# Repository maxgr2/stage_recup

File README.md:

# Projet de Surveillance de Batteries

## Introduction 

Ce repo a été réalisé dans le cadre d'un stage de 4ème année d'école d'ingénieurs à l'**École de Technologie Supérieure (ÉTS) de Montréal**, au sein du laboratoire **LACIME**, par un étudiant de **Polytech Grenoble**.
Si vous souhaitez avoir plus de détails sur le contenu de chaque projet merci de suivre les dossier projet_batterie et projet_salle_blanche.
Le dossier contient aussi tous les fichiers Kicad, Le dossier Kicad contient les évolutions des différentes cartes produites et la dernière version est celle à jour pour le projet batterie.
Le dossier Kicad esp maitre est le dossier principale pour le projet salle blanche.

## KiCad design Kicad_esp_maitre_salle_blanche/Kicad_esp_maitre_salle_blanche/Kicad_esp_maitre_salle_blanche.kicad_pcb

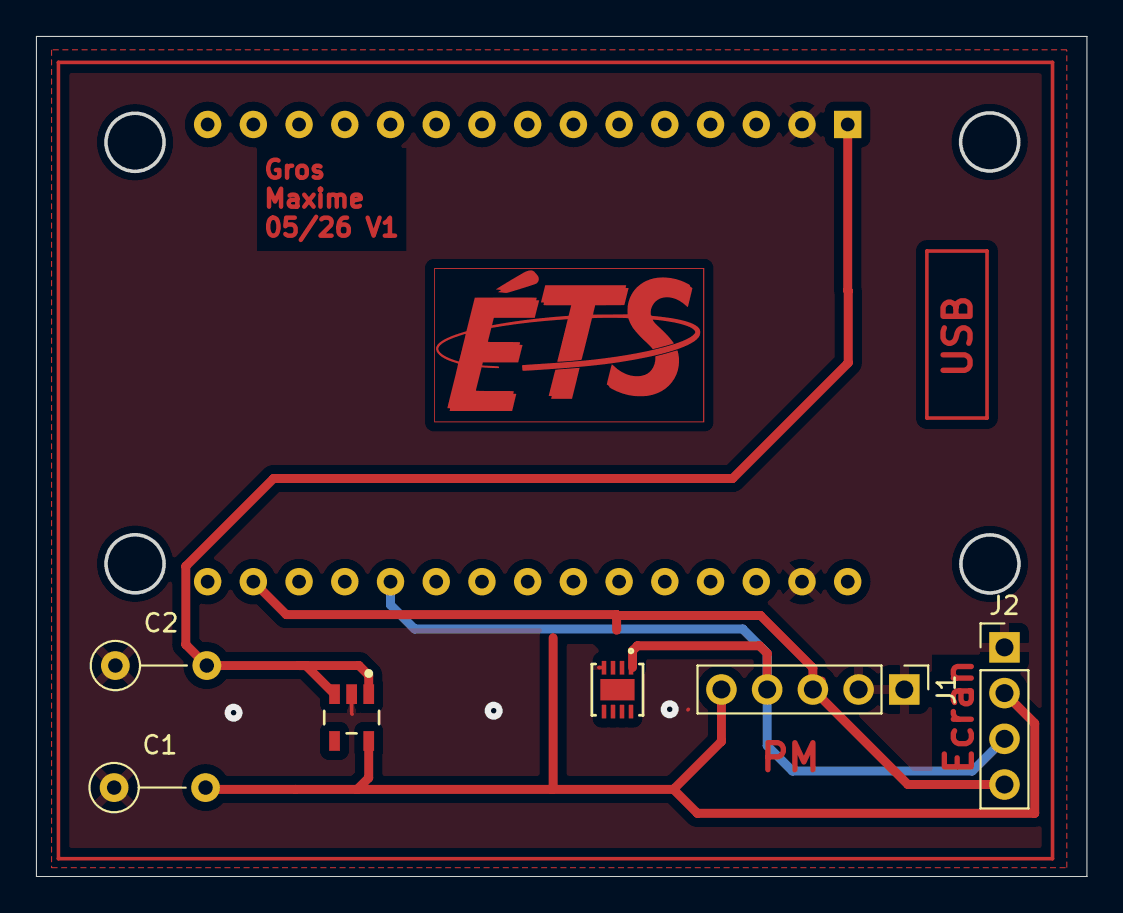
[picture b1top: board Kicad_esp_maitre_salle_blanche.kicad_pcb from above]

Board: 2 copper layers, 58.4 x 46.7 mm, 7 parts (1 on the bottom side), 5 nets.

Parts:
C1, C2: C; R_Axial_DIN0207_L6.3mm_D2.5mm_P5.08mm_Vertical
J1: Conn_01x05_Pin; PinHeader_1x05_P2.54mm_Vertical
J2: Conn_01x04_Pin; PinHeader_1x04_P2.54mm_Vertical
U1: esp32_devkit_v1_doit
U2: TLV75533PDYDR; DBV0005A-MFG
U3: SHT40-CD1B-R3; U_SHT3_SEN

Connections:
5V: C2.2, U1.1 (VIN), U2.1 (IN), U2.3 (EN)
5V_LDO: C1.2, J1.5, J2.2, U2.5 (OUT), U3.3 (VDD)
GND: C1.1, C2.1, J1.1, J1.2, J2.1, U1.2 (GND), U1.17 (GND), U2.2 (GND), U3.4 (VSS)
SCL: J1.3, J2.4, U1.29 (GPIO22), U3.2 (SCL)
SDA: J1.4, J2.3, U1.26 (GPIO21), U3.1 (SDA)

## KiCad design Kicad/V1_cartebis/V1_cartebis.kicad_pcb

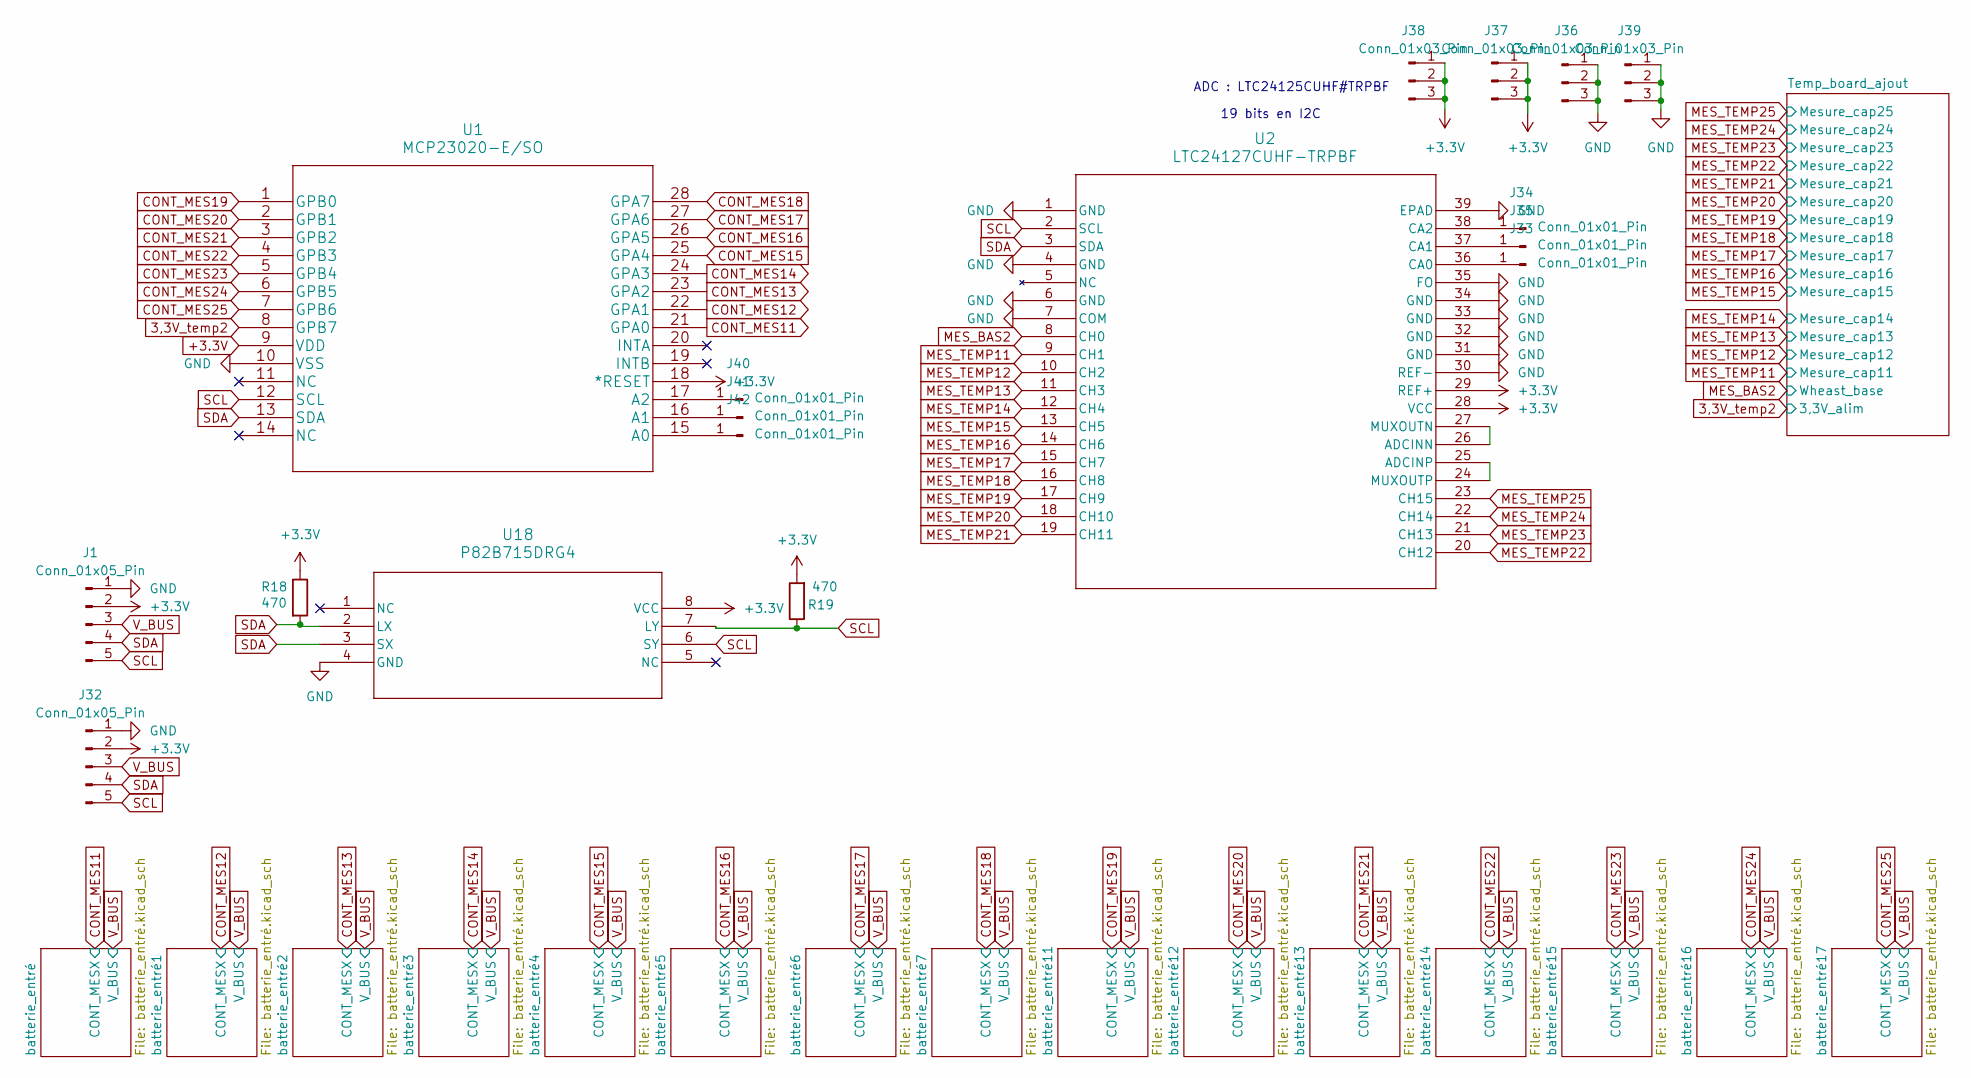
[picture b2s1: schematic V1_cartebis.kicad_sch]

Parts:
J1, J32: Conn_01x05_Pin; PinHeader_1x05_P2.54mm_Vertical
J33, J34, J35, J40, J41, J42: Conn_01x01_Pin; PinHeader_1x01_P1.00mm_Vertical
J36, J37, J38, J39: Conn_01x03_Pin; PinHeader_1x03_P1.00mm_Vertical
R18, R19: 470; R_Axial_DIN0207_L6.3mm_D2.5mm_P10.16mm_Horizontal
U1: MCP23020-E/SO; MCP23017T-E&slash_SO
U2: LTC24127CUHF-TRPBF; QFN-38_UHF_LIT
U18: P82B715DRG4

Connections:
3,3V_temp2: U1.8 (GPB7); also elsewhere on the board
+3.3V: J1.2, J32.2, J37.1, J37.2, J37.3, J38.1, J38.2, J38.3, R18.1, R19.2, U1.9 (VDD), U1.18 (*RESET), U2.28 (VCC), U2.29 (REF+), U18.8 (VCC)
CONT_MES11: U1.21 (GPA0); also elsewhere on the board
CONT_MES12: U1.22 (GPA1); also elsewhere on the board
CONT_MES13: U1.23 (GPA2); also elsewhere on the board
CONT_MES14: U1.24 (GPA3); also elsewhere on the board
CONT_MES15: U1.25 (GPA4); also elsewhere on the board
CONT_MES16: U1.26 (GPA5); also elsewhere on the board
CONT_MES17: U1.27 (GPA6); also elsewhere on the board
CONT_MES18: U1.28 (GPA7); also elsewhere on the board
CONT_MES19: U1.1 (GPB0); also elsewhere on the board
CONT_MES20: U1.2 (GPB1); also elsewhere on the board
CONT_MES21: U1.3 (GPB2); also elsewhere on the board
CONT_MES22: U1.4 (GPB3); also elsewhere on the board
CONT_MES23: U1.5 (GPB4); also elsewhere on the board
CONT_MES24: U1.6 (GPB5); also elsewhere on the board
CONT_MES25: U1.7 (GPB6); also elsewhere on the board
GND: J1.1, J32.1, J36.1, J36.2, J36.3, J39.1, J39.2, J39.3, U1.10 (VSS), U2.1 (GND), U2.4 (GND), U2.6 (GND), U2.7 (COM), U2.30 (REF-), U2.31 (GND), U2.32 (GND), U2.33 (GND), U2.34 (GND), U2.35 (FO), U2.39 (EPAD), U18.4 (GND); also elsewhere on the board
MES_BAS2: U2.8 (CH0); also elsewhere on the board
MES_TEMP11: U2.9 (CH1); also elsewhere on the board
MES_TEMP12: U2.10 (CH2); also elsewhere on the board
MES_TEMP13: U2.11 (CH3); also elsewhere on the board
MES_TEMP14: U2.12 (CH4); also elsewhere on the board
MES_TEMP15: U2.13 (CH5); also elsewhere on the board
MES_TEMP16: U2.14 (CH6); also elsewhere on the board
MES_TEMP17: U2.15 (CH7); also elsewhere on the board
MES_TEMP18: U2.16 (CH8); also elsewhere on the board
MES_TEMP19: U2.17 (CH9); also elsewhere on the board
MES_TEMP20: U2.18 (CH10); also elsewhere on the board
MES_TEMP21: U2.19 (CH11); also elsewhere on the board
MES_TEMP22: U2.20 (CH12); also elsewhere on the board
MES_TEMP23: U2.21 (CH13); also elsewhere on the board
MES_TEMP24: U2.22 (CH14); also elsewhere on the board
MES_TEMP25: U2.23 (CH15); also elsewhere on the board
unnamed: J33.1, U2.36 (CA0)
unnamed: J34.1, U2.38 (CA2)
unnamed: J35.1, U2.37 (CA1)
unnamed: J40.1, U1.17 (A2)
unnamed: J41.1, U1.16 (A1)
unnamed: J42.1, U1.15 (A0)
unnamed: U2.26 (ADCINN), U2.27 (MUXOUTN)
unnamed: U2.24 (MUXOUTP), U2.25 (ADCINP)
SCL: J1.5, J32.5, R19.1, U1.12 (SCL), U2.2 (SCL), U18.6 (SY), U18.7 (LY)
SDA: J1.4, J32.4, R18.2, U1.13 (SDA), U2.3 (SDA), U18.2 (LX), U18.3 (SX)
V_BUS: J1.3, J32.3; also elsewhere on the board

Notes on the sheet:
19 bits en I2C
ADC : LTC24125CUHF#TRPBF

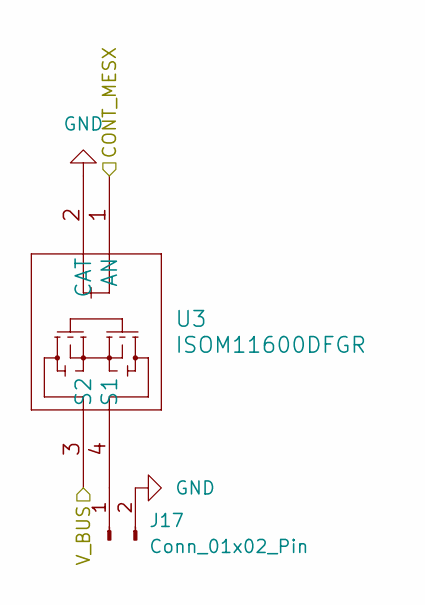
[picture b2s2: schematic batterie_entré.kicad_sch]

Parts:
J17: Conn_01x02_Pin; PinHeader_1x02_P2.54mm_Vertical
U3: ISOM11600DFGR; ISOM8600DFGR

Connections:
CONT_MES19: U3.1 (AN); also elsewhere on the board
GND: J17.2, U3.2 (CAT); also elsewhere on the board
unnamed: J17.1, U3.4 (S1)
V_BUS: U3.3 (S2); also elsewhere on the board

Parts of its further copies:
J18, J19, J20, J21, J22, J23, J24, J25, J26, J27, J28, J29, J30, J31: Conn_01x02_Pin; PinHeader_1x02_P2.54mm_Vertical
U4, U5, U6, U7, U8, U9, U10, U11, U12, U13, U14, U15, U16, U17: ISOM11600DFGR; ISOM8600DFGR

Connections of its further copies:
CONT_MES11: U14.1 (AN); also elsewhere on the board
CONT_MES12: U15.1 (AN); also elsewhere on the board
CONT_MES13: U16.1 (AN); also elsewhere on the board
CONT_MES14: U17.1 (AN); also elsewhere on the board
CONT_MES15: U11.1 (AN); also elsewhere on the board
CONT_MES16: U10.1 (AN); also elsewhere on the board
CONT_MES17: U13.1 (AN); also elsewhere on the board
CONT_MES18: U12.1 (AN); also elsewhere on the board
CONT_MES20: U4.1 (AN); also elsewhere on the board
CONT_MES21: U9.1 (AN); also elsewhere on the board
CONT_MES22: U8.1 (AN); also elsewhere on the board
CONT_MES23: U6.1 (AN); also elsewhere on the board
CONT_MES24: U5.1 (AN); also elsewhere on the board
CONT_MES25: U7.1 (AN); also elsewhere on the board
GND: J18.2, J19.2, J20.2, J21.2, J22.2, J23.2, J24.2, J25.2, J26.2, J27.2, J28.2, J29.2, J30.2, J31.2, U4.2 (CAT), U5.2 (CAT), U6.2 (CAT), U7.2 (CAT), U8.2 (CAT), U9.2 (CAT), U10.2 (CAT), U11.2 (CAT), U12.2 (CAT), U13.2 (CAT), U14.2 (CAT), U15.2 (CAT), U16.2 (CAT), U17.2 (CAT); also elsewhere on the board
unnamed: J18.1, U4.4 (S1)
unnamed: J19.1, U5.4 (S1)
unnamed: J20.1, U6.4 (S1)
unnamed: J21.1, U7.4 (S1)
unnamed: J22.1, U8.4 (S1)
unnamed: J23.1, U9.4 (S1)
unnamed: J24.1, U10.4 (S1)
unnamed: J25.1, U11.4 (S1)
unnamed: J26.1, U12.4 (S1)
unnamed: J27.1, U13.4 (S1)
unnamed: J28.1, U14.4 (S1)
unnamed: J29.1, U15.4 (S1)
unnamed: J30.1, U16.4 (S1)
unnamed: J31.1, U17.4 (S1)
V_BUS: U4.3 (S2), U5.3 (S2), U6.3 (S2), U7.3 (S2), U8.3 (S2), U9.3 (S2), U10.3 (S2), U11.3 (S2), U12.3 (S2), U13.3 (S2), U14.3 (S2), U15.3 (S2), U16.3 (S2), U17.3 (S2); also elsewhere on the board

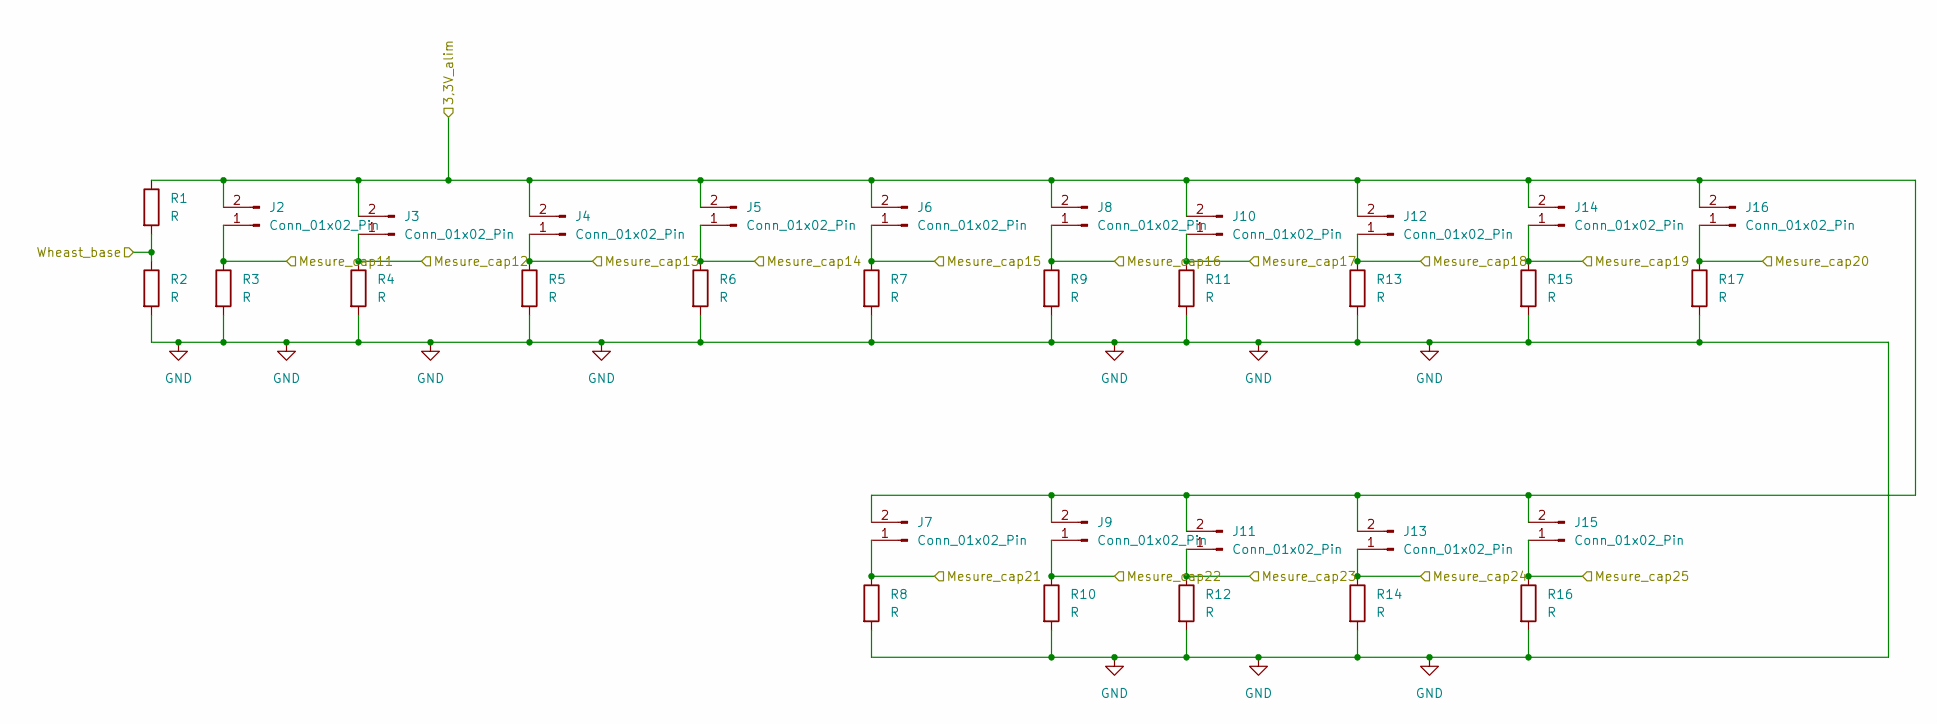
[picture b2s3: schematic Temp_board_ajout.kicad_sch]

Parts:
J2, J3, J4, J5, J6, J7, J8, J9, J10, J11, J12, J13, J14, J15, J16: Conn_01x02_Pin; PinHeader_1x02_P2.54mm_Vertical
R1, R2, R3, R4, R5, R6, R7, R8, R9, R10, R11, R12, R13, R14, R15, R16, R17: R; R_Axial_DIN0207_L6.3mm_D2.5mm_P10.16mm_Horizontal

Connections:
3,3V_temp2: J2.2, J3.2, J4.2, J5.2, J6.2, J7.2, J8.2, J9.2, J10.2, J11.2, J12.2, J13.2, J14.2, J15.2, J16.2, R1.1; also elsewhere on the board
GND: R2.2, R3.2, R4.2, R5.2, R6.2, R7.2, R8.2, R9.2, R10.2, R11.2, R12.2, R13.2, R14.2, R15.2, R16.2, R17.2; also elsewhere on the board
MES_BAS2: R1.2, R2.1; also elsewhere on the board
MES_TEMP11: J2.1, R3.1; also elsewhere on the board
MES_TEMP12: J3.1, R4.1; also elsewhere on the board
MES_TEMP13: J4.1, R5.1; also elsewhere on the board
MES_TEMP14: J5.1, R6.1; also elsewhere on the board
MES_TEMP15: J6.1, R7.1; also elsewhere on the board
MES_TEMP16: J8.1, R9.1; also elsewhere on the board
MES_TEMP17: J10.1, R11.1; also elsewhere on the board
MES_TEMP18: J12.1, R13.1; also elsewhere on the board
MES_TEMP19: J14.1, R15.1; also elsewhere on the board
MES_TEMP20: J16.1, R17.1; also elsewhere on the board
MES_TEMP21: J7.1, R8.1; also elsewhere on the board
MES_TEMP22: J9.1, R10.1; also elsewhere on the board
MES_TEMP23: J11.1, R12.1; also elsewhere on the board
MES_TEMP24: J13.1, R14.1; also elsewhere on the board
MES_TEMP25: J15.1, R16.1; also elsewhere on the board

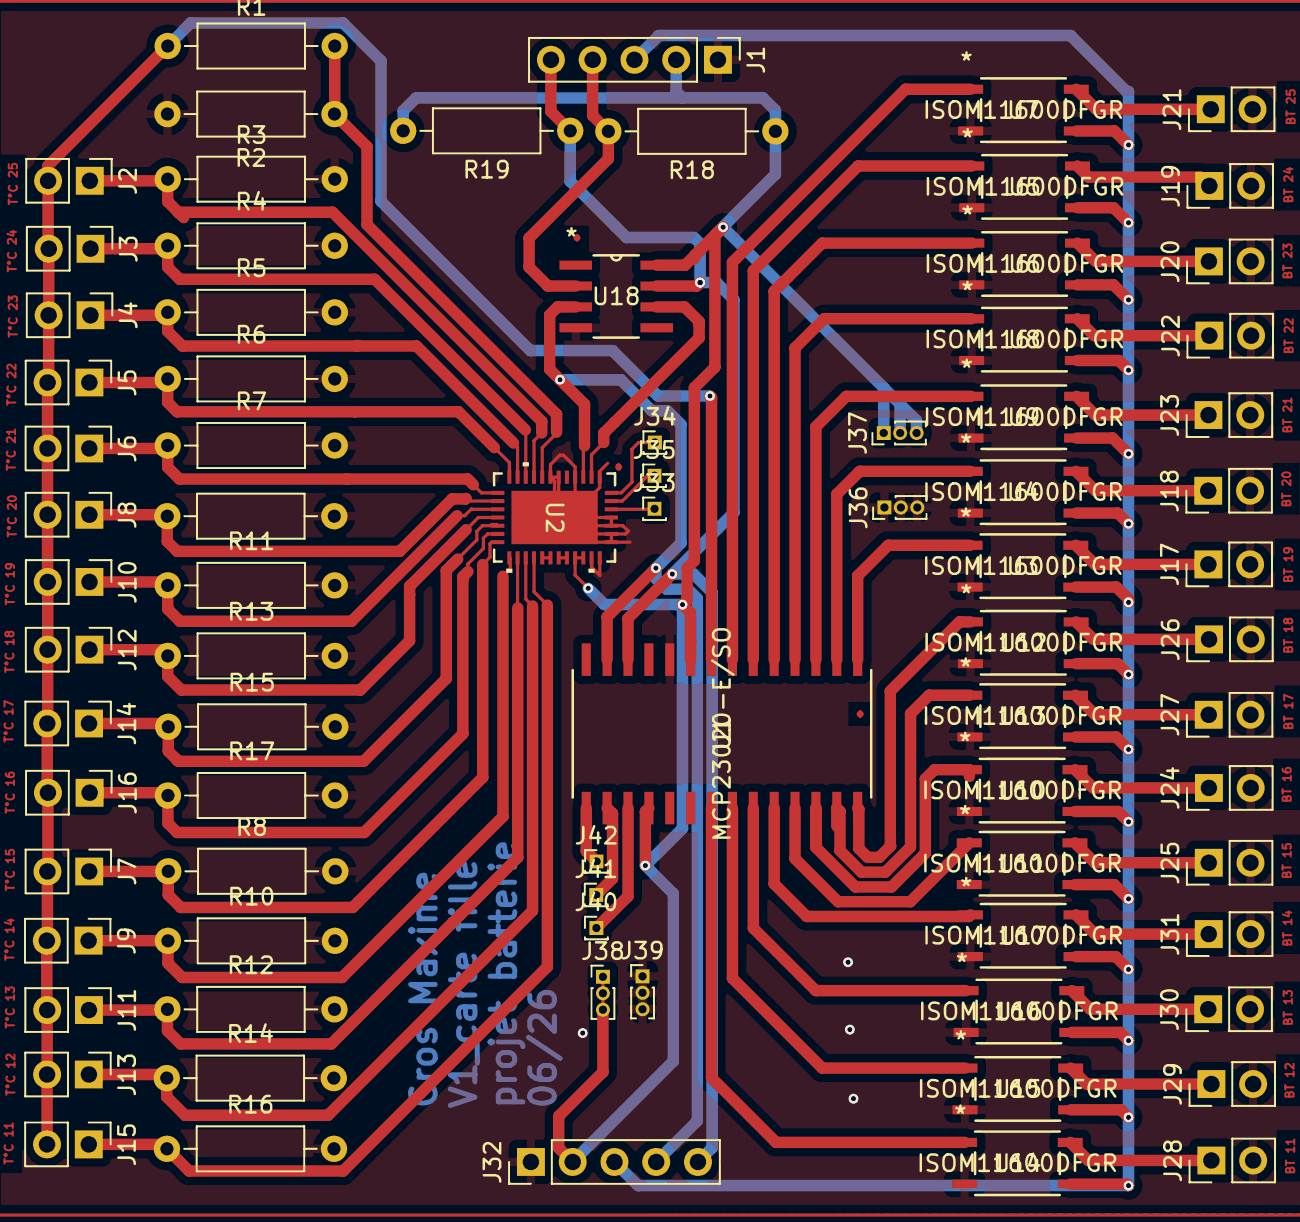
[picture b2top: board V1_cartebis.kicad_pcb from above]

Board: 2 copper layers, 79 parts (0 on the bottom side), 60 nets.

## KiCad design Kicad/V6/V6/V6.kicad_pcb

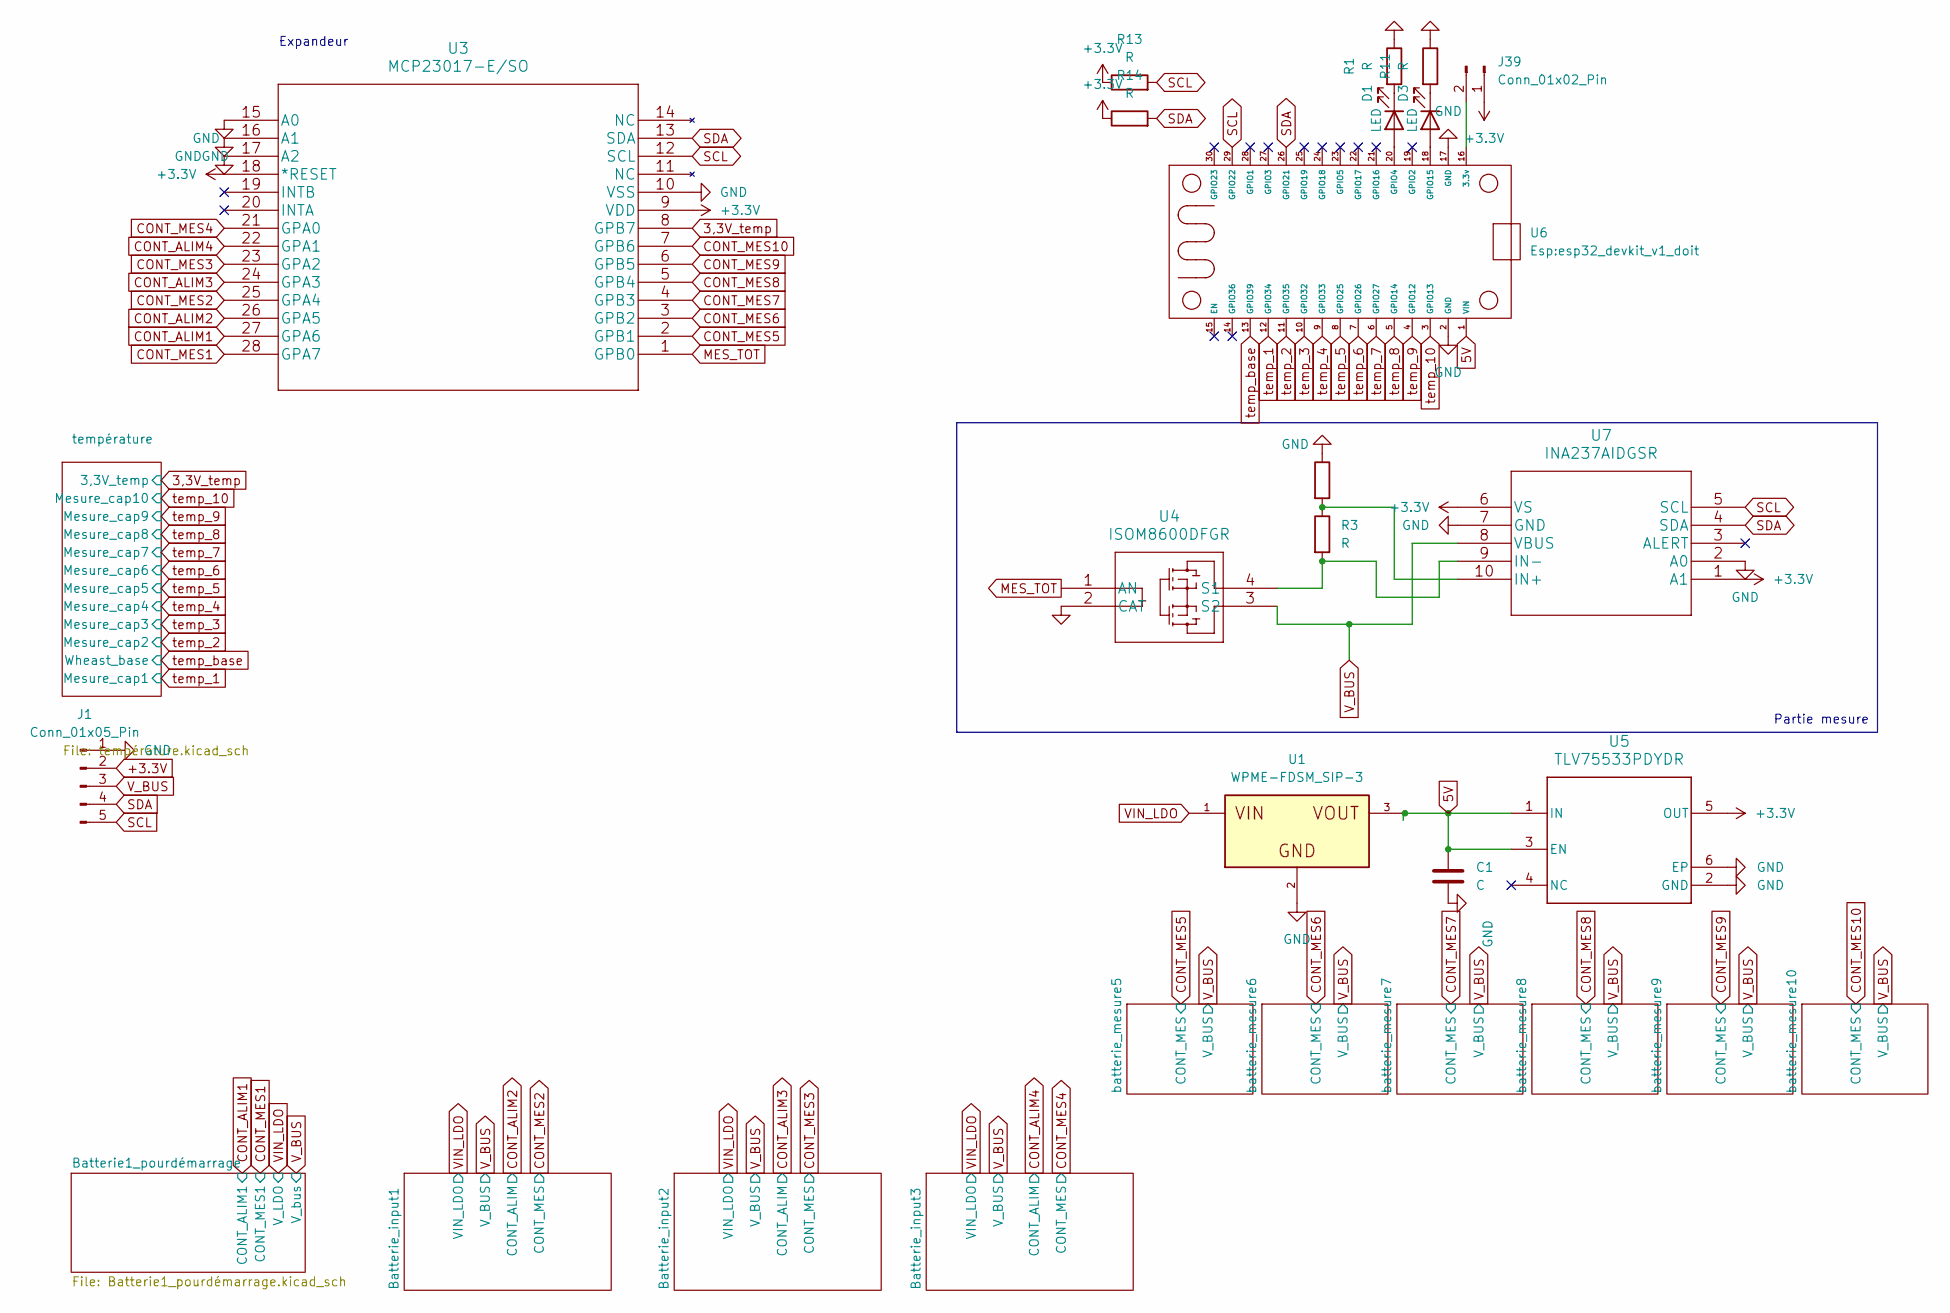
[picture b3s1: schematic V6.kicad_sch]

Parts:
C1: C; R_Axial_DIN0207_L6.3mm_D2.5mm_P5.08mm_Vertical
D1, D3: LED; PinHeader_1x02_P2.54mm_Vertical
J1: Conn_01x05_Pin; PinHeader_1x05_P2.54mm_Vertical
J39: Conn_01x02_Pin; PinHeader_1x02_P2.54mm_Vertical
R1, R11, R13, R14: R; R_Axial_DIN0207_L6.3mm_D2.5mm_P10.16mm_Horizontal
R2: 2,2Kohms; R_Axial_DIN0309_L9.0mm_D3.2mm_P20.32mm_Horizontal
R3: R; R_Axial_DIN0411_L9.9mm_D3.6mm_P20.32mm_Horizontal
U1: WPME-FDSM_SIP-3; WPME-FDSM_173950575
U3: MCP23017-E/SO; MCP23017T-E&slash_SO
U4: ISOM8600DFGR
U5: TLV75533PDYDR
U6: esp32_devkit_v1_doit
U7: INA237AIDGSR

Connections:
3,3V_temp: U3.8 (GPB7); also elsewhere on the board
5V: C1.2, U1.3, U5.1 (IN), U5.3 (EN), U6.1 (VIN)
+3.3V: J1.2, J39.1, R13.1, R14.1, U3.9 (VDD), U3.18 (*RESET), U5.5 (OUT), U7.1 (A1), U7.6 (VS)
CONT_ALIM1: U3.27 (GPA6); also elsewhere on the board
CONT_ALIM2: U3.26 (GPA5); also elsewhere on the board
CONT_ALIM3: U3.24 (GPA3); also elsewhere on the board
CONT_ALIM4: U3.22 (GPA1); also elsewhere on the board
CONT_MES1: U3.28 (GPA7); also elsewhere on the board
CONT_MES2: U3.25 (GPA4); also elsewhere on the board
CONT_MES3: U3.23 (GPA2); also elsewhere on the board
CONT_MES4: U3.21 (GPA0); also elsewhere on the board
CONT_MES5: U3.2 (GPB1); also elsewhere on the board
CONT_MES6: U3.3 (GPB2); also elsewhere on the board
CONT_MES7: U3.4 (GPB3); also elsewhere on the board
CONT_MES8: U3.5 (GPB4); also elsewhere on the board
CONT_MES9: U3.6 (GPB5); also elsewhere on the board
CONT_MES10: U3.7 (GPB6); also elsewhere on the board
GND: C1.1, J1.1, R1.1, R2.1, R11.1, U1.2, U3.10 (VSS), U3.15 (A0), U3.16 (A1), U3.17 (A2), U4.2 (CAT), U5.2 (GND), U5.6 (EP), U6.2 (GND), U6.17 (GND), U7.2 (A0), U7.7 (GND); also elsewhere on the board
MES_TOT: U3.1 (GPB0), U4.1 (AN)
unnamed: D1.2 (A), U6.20 (GPIO4)
unnamed: D1.1 (K), R1.2
unnamed: D3.2 (A), U6.18 (GPIO15)
unnamed: D3.1 (K), R11.2
unnamed: J39.2, U6.16 (3.3v)
unnamed: R3.2, U4.4 (S1), U7.9 (IN-)
unnamed: R2.2, R3.1, U7.10 (IN+)
SCL: J1.5, R13.2, U3.12 (SCL), U6.29 (GPIO22), U7.5 (SCL)
SDA: J1.4, R14.2, U3.13 (SDA), U6.26 (GPIO21), U7.4 (SDA)
VIN_LDO: U1.1; also elsewhere on the board
V_BUS: J1.3, U4.3 (S2), U7.8 (VBUS); also elsewhere on the board
temp_1: U6.12 (GPIO34); also elsewhere on the board
temp_2: U6.11 (GPIO35); also elsewhere on the board
temp_3: U6.10 (GPIO32); also elsewhere on the board
temp_4: U6.9 (GPIO33); also elsewhere on the board
temp_5: U6.8 (GPIO25); also elsewhere on the board
temp_6: U6.7 (GPIO26); also elsewhere on the board
temp_7: U6.6 (GPIO27); also elsewhere on the board
temp_8: U6.5 (GPIO14); also elsewhere on the board
temp_9: U6.4 (GPIO12); also elsewhere on the board
temp_10: U6.3 (GPIO13); also elsewhere on the board
temp_base: U6.13 (GPIO39); also elsewhere on the board

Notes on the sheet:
Partie mesure
Expandeur

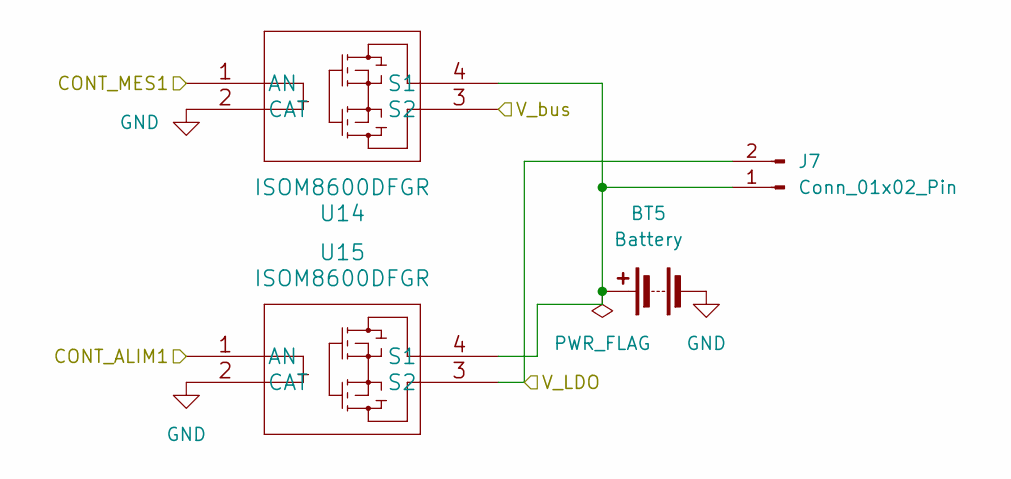
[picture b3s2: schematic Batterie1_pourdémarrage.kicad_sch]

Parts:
BT5: Battery; R_Axial_DIN0207_L6.3mm_D2.5mm_P5.08mm_Vertical
J7: Conn_01x02_Pin; PinHeader_1x02_P2.54mm_Vertical
U14, U15: ISOM8600DFGR

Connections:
CONT_ALIM1: U15.1 (AN); also elsewhere on the board
CONT_MES1: U14.1 (AN); also elsewhere on the board
GND: BT5.2 (-), U14.2 (CAT), U15.2 (CAT); also elsewhere on the board
unnamed: BT5.1 (+), J7.1, U14.4 (S1), U15.4 (S1)
VIN_LDO: J7.2, U15.3 (S2); also elsewhere on the board
V_BUS: U14.3 (S2); also elsewhere on the board

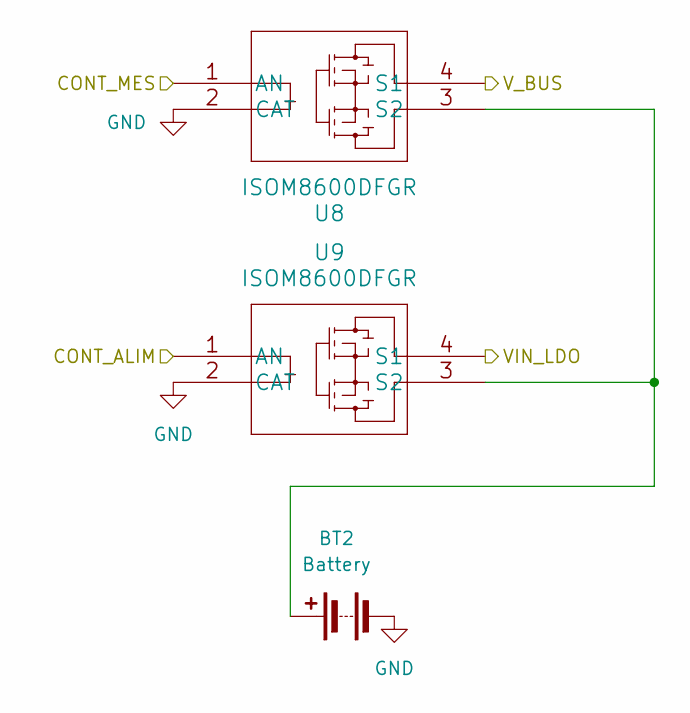
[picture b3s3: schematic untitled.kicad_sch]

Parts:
BT2: Battery; R_Axial_DIN0207_L6.3mm_D2.5mm_P5.08mm_Vertical
U8, U9: ISOM8600DFGR

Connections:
CONT_ALIM2: U9.1 (AN); also elsewhere on the board
CONT_MES2: U8.1 (AN); also elsewhere on the board
GND: BT2.2 (-), U8.2 (CAT), U9.2 (CAT); also elsewhere on the board
unnamed: BT2.1 (+), U8.3 (S2), U9.3 (S2)
VIN_LDO: U9.4 (S1); also elsewhere on the board
V_BUS: U8.4 (S1); also elsewhere on the board

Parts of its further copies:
BT3, BT4: Battery; R_Axial_DIN0207_L6.3mm_D2.5mm_P5.08mm_Vertical
U10, U11, U12, U13: ISOM8600DFGR

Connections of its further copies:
CONT_ALIM3: U11.1 (AN); also elsewhere on the board
CONT_ALIM4: U13.1 (AN); also elsewhere on the board
CONT_MES3: U10.1 (AN); also elsewhere on the board
CONT_MES4: U12.1 (AN); also elsewhere on the board
GND: BT3.2 (-), BT4.2 (-), U10.2 (CAT), U11.2 (CAT), U12.2 (CAT), U13.2 (CAT); also elsewhere on the board
unnamed: BT3.1 (+), U10.3 (S2), U11.3 (S2)
unnamed: BT4.1 (+), U12.3 (S2), U13.3 (S2)
VIN_LDO: U11.4 (S1), U13.4 (S1); also elsewhere on the board
V_BUS: U10.4 (S1), U12.4 (S1); also elsewhere on the board

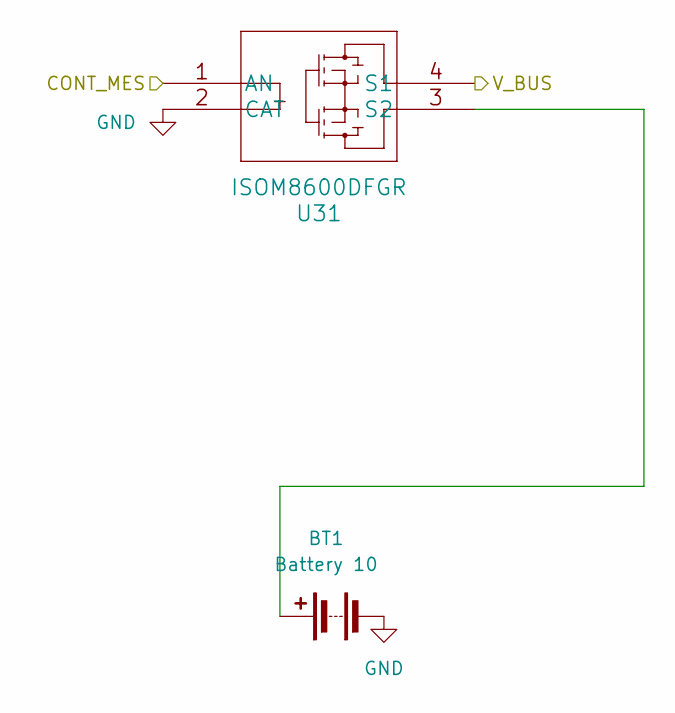
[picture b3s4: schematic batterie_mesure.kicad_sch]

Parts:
BT1: Battery 10; R_Axial_DIN0207_L6.3mm_D2.5mm_P5.08mm_Vertical
U31: ISOM8600DFGR

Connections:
CONT_MES10: U31.1 (AN); also elsewhere on the board
GND: BT1.2 (-), U31.2 (CAT); also elsewhere on the board
unnamed: BT1.1 (+), U31.3 (S2)
V_BUS: U31.4 (S1); also elsewhere on the board

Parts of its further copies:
BT6, BT7, BT8, BT9, BT10: Battery 10; R_Axial_DIN0207_L6.3mm_D2.5mm_P5.08mm_Vertical
U32, U33, U34, U35, U36: ISOM8600DFGR

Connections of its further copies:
CONT_MES5: U36.1 (AN); also elsewhere on the board
CONT_MES6: U35.1 (AN); also elsewhere on the board
CONT_MES7: U34.1 (AN); also elsewhere on the board
CONT_MES8: U33.1 (AN); also elsewhere on the board
CONT_MES9: U32.1 (AN); also elsewhere on the board
GND: BT6.2 (-), BT7.2 (-), BT8.2 (-), BT9.2 (-), BT10.2 (-), U32.2 (CAT), U33.2 (CAT), U34.2 (CAT), U35.2 (CAT), U36.2 (CAT); also elsewhere on the board
unnamed: BT6.1 (+), U32.3 (S2)
unnamed: BT7.1 (+), U33.3 (S2)
unnamed: BT8.1 (+), U34.3 (S2)
unnamed: BT9.1 (+), U35.3 (S2)
unnamed: BT10.1 (+), U36.3 (S2)
V_BUS: U32.4 (S1), U33.4 (S1), U34.4 (S1), U35.4 (S1), U36.4 (S1); also elsewhere on the board

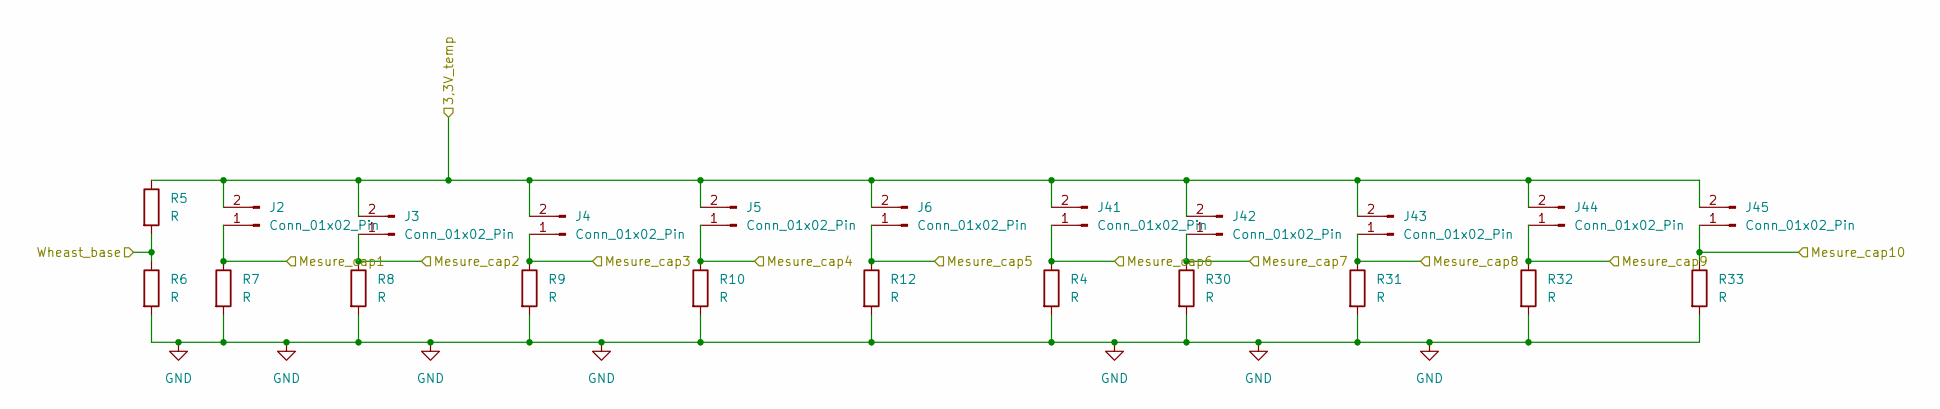
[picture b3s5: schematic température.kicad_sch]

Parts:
J2, J3, J4, J5, J6, J41, J42, J43, J44, J45: Conn_01x02_Pin; PinHeader_1x02_P2.54mm_Vertical
R4, R5, R6, R7, R8, R9, R10, R12, R30, R31, R32, R33: R; R_Axial_DIN0207_L6.3mm_D2.5mm_P10.16mm_Horizontal

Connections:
3,3V_temp: J2.2, J3.2, J4.2, J5.2, J6.2, J41.2, J42.2, J43.2, J44.2, J45.2, R5.1; also elsewhere on the board
GND: R4.2, R6.2, R7.2, R8.2, R9.2, R10.2, R12.2, R30.2, R31.2, R32.2, R33.2; also elsewhere on the board
temp_1: J2.1, R7.1; also elsewhere on the board
temp_2: J3.1, R8.1; also elsewhere on the board
temp_3: J4.1, R9.1; also elsewhere on the board
temp_4: J5.1, R10.1; also elsewhere on the board
temp_5: J6.1, R12.1; also elsewhere on the board
temp_6: J41.1, R4.1; also elsewhere on the board
temp_7: J42.1, R30.1; also elsewhere on the board
temp_8: J43.1, R31.1; also elsewhere on the board
temp_9: J44.1, R32.1; also elsewhere on the board
temp_10: J45.1, R33.1; also elsewhere on the board
temp_base: R5.2, R6.1; also elsewhere on the board

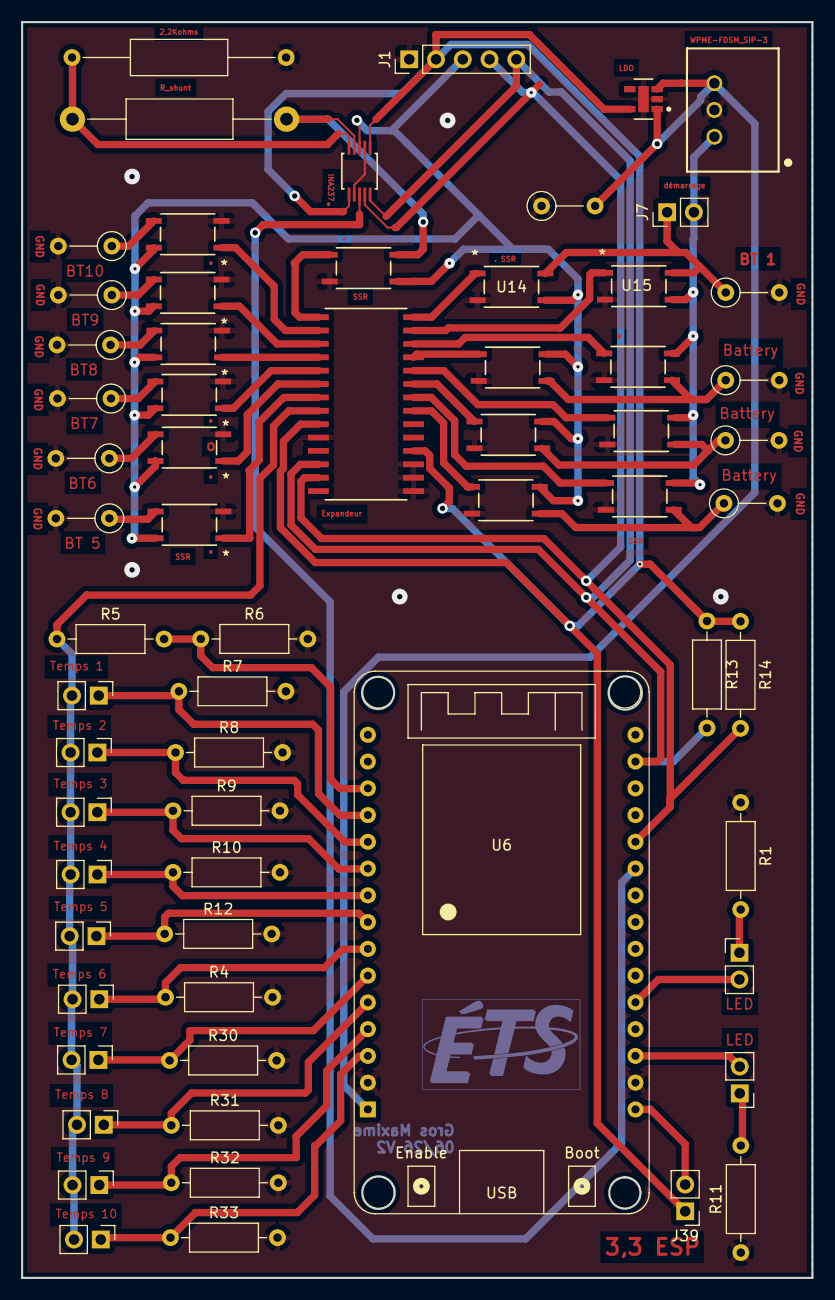
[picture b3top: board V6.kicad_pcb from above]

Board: 2 copper layers, 75.0 x 119.2 mm, 64 parts (0 on the bottom side), 51 nets.

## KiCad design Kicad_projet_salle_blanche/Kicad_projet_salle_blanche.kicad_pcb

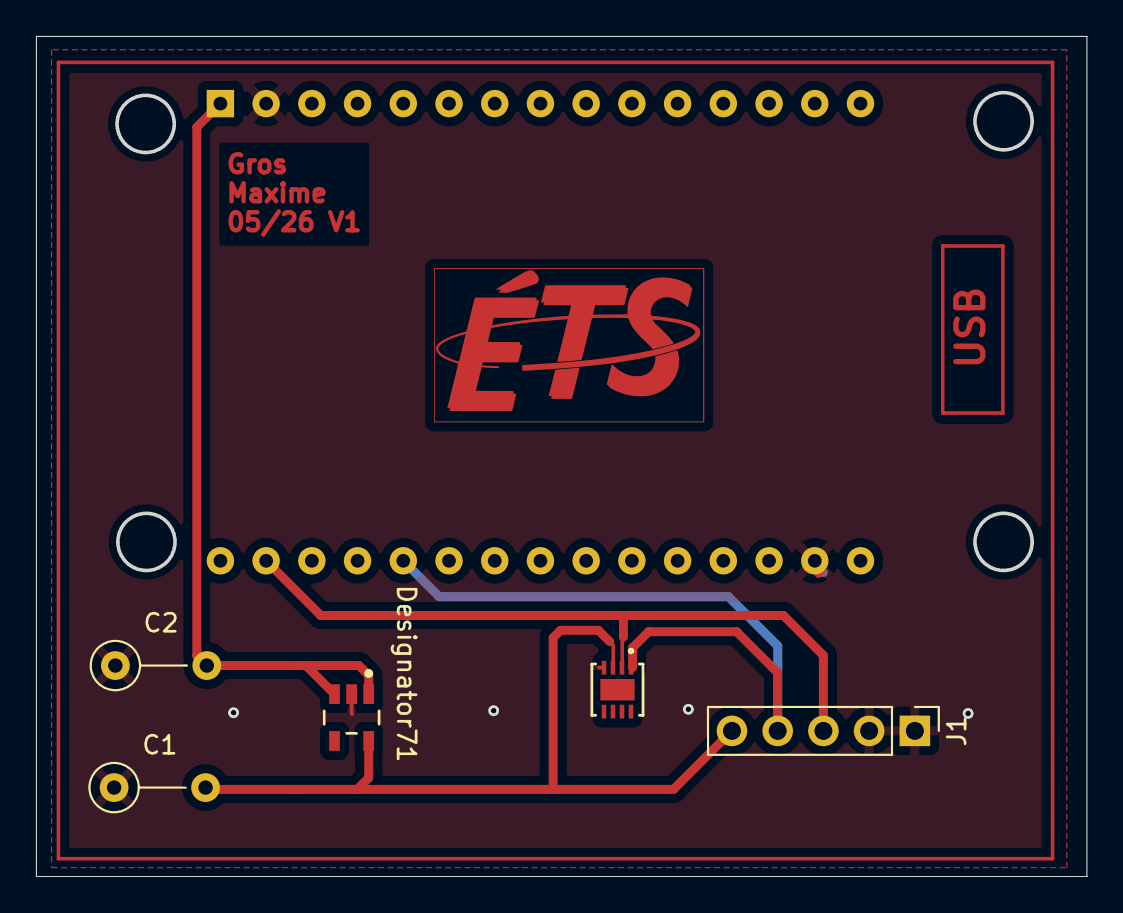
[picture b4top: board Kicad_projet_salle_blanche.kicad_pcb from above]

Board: 2 copper layers, 58.4 x 46.7 mm, 6 parts (1 on the bottom side), 5 nets.

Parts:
C1, C2: C; R_Axial_DIN0207_L6.3mm_D2.5mm_P5.08mm_Vertical
J1: Conn_01x05_Pin; PinHeader_1x05_P2.54mm_Vertical
U1: esp32_devkit_v1_doit
U2: TLV75533PDYDR; DBV0005A-MFG
U3: SHT40-CD1B-R3; U_SHT3_SEN

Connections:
5V: C2.2, U1.1 (VIN), U2.1 (IN), U2.3 (EN)
5V_LDO: C1.2, J1.5, U2.5 (OUT), U3.3 (VDD)
GND: C1.1, C2.1, J1.1, J1.2, U1.2 (GND), U1.17 (GND), U2.2 (GND), U3.4 (VSS)
SCL: J1.3, U1.29 (GPIO22), U3.2 (SCL)
SDA: J1.4, U1.26 (GPIO21), U3.1 (SDA)

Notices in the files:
parts and their libraries:
Copyright 2016 Accelerated Designs. All rights reserved.
